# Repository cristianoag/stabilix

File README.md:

# Stabilix

Stabilix is a spin-off of the self-balancing robot project called B-ROBOT EVO created by JJ Robotics. 

It is a platform for experiments with different sensors and algorithms. The robot is able to balance itself on two wheels and move around avoiding obstacles. The robot is based on ESP32 and it is remotely controlled using a smartphone via Bluetooth.

## Hardware

The robot is based on ESP32 microcontroller and it is remotely controlled using a smartphone via Bluetooth. The robot is equipped with the following hardware components:

* 1 x MPU6050 - 6-axis accelerometer and gyroscope
* 2 x NEMA17 stepper motors
* 2 x A4988 stepper motor drivers
* 1 x ESP32 microcontroller

The robot is powered by a 7.4V LIPO battery pack. The battery is connected to a voltage regulator that converts the voltage to 5V. The 5V is used to power the ESP32 microcontroller and the stepper motor drivers. The stepper motors are powered directly from the battery.

## Assembly

The robot is assembled using 3D printed parts. The 3D models are available in the `3D_models` folder. The robot is assembled using the following parts:

### Bill of materials

| Part name | Quantity | Link |
| --- | --- | --- |
| 3D printed parts | 1 | [Thingiverse](https://www.thingiverse.com/thing:2786294) |

## Software

The robot is programmed in C++ using Arduino IDE. The code is based on the B-ROBOT EVO project created by JJ Robotics. 

## Installation

1. Download and install Arduino IDE from [here](https://www.arduino.cc/en/software)
2. Download and install ESP32 board support for Arduino IDE from [here]()
3. Download the code from this repository and open it in Arduino IDE
4. Connect the robot to your computer using a USB cable
5. Select the correct board and port in Arduino IDE
6. Upload the code to the robot

## Usage

1. Download and install the B-ROBOT EVO app from [here](https://play.google.com/store/apps/details?id=com.jjrobots.brobotevoremotecontrol&hl=en&gl=US)

2. Turn on the robot and connect to it using the app

3. Use the app to control the robot

## Contributing

Pull requests are welcome. For major changes, please open an issue first to discuss what you would like to change.

## License

This work is licensed under the CERN OHL-S v2. You may redistribute and modify this project and its documentation under the terms of the CERN-OHL-S v2.

This project is distributed WITHOUT ANY EXPRESS OR IMPLIED WARRANTY, INCLUDING OF MERCHANTABILITY, SATISFACTORY QUALITY AND FITNESS FOR A PARTICULAR PURPOSE. Please see the CERN-OHL-S v2 for applicable conditions.

You should have received a copy of the CERN-OHL-S along with this project. If not, see <https://ohwr.org/project/cernohl/wikis/Documents/CERN-OHL-version-2>.

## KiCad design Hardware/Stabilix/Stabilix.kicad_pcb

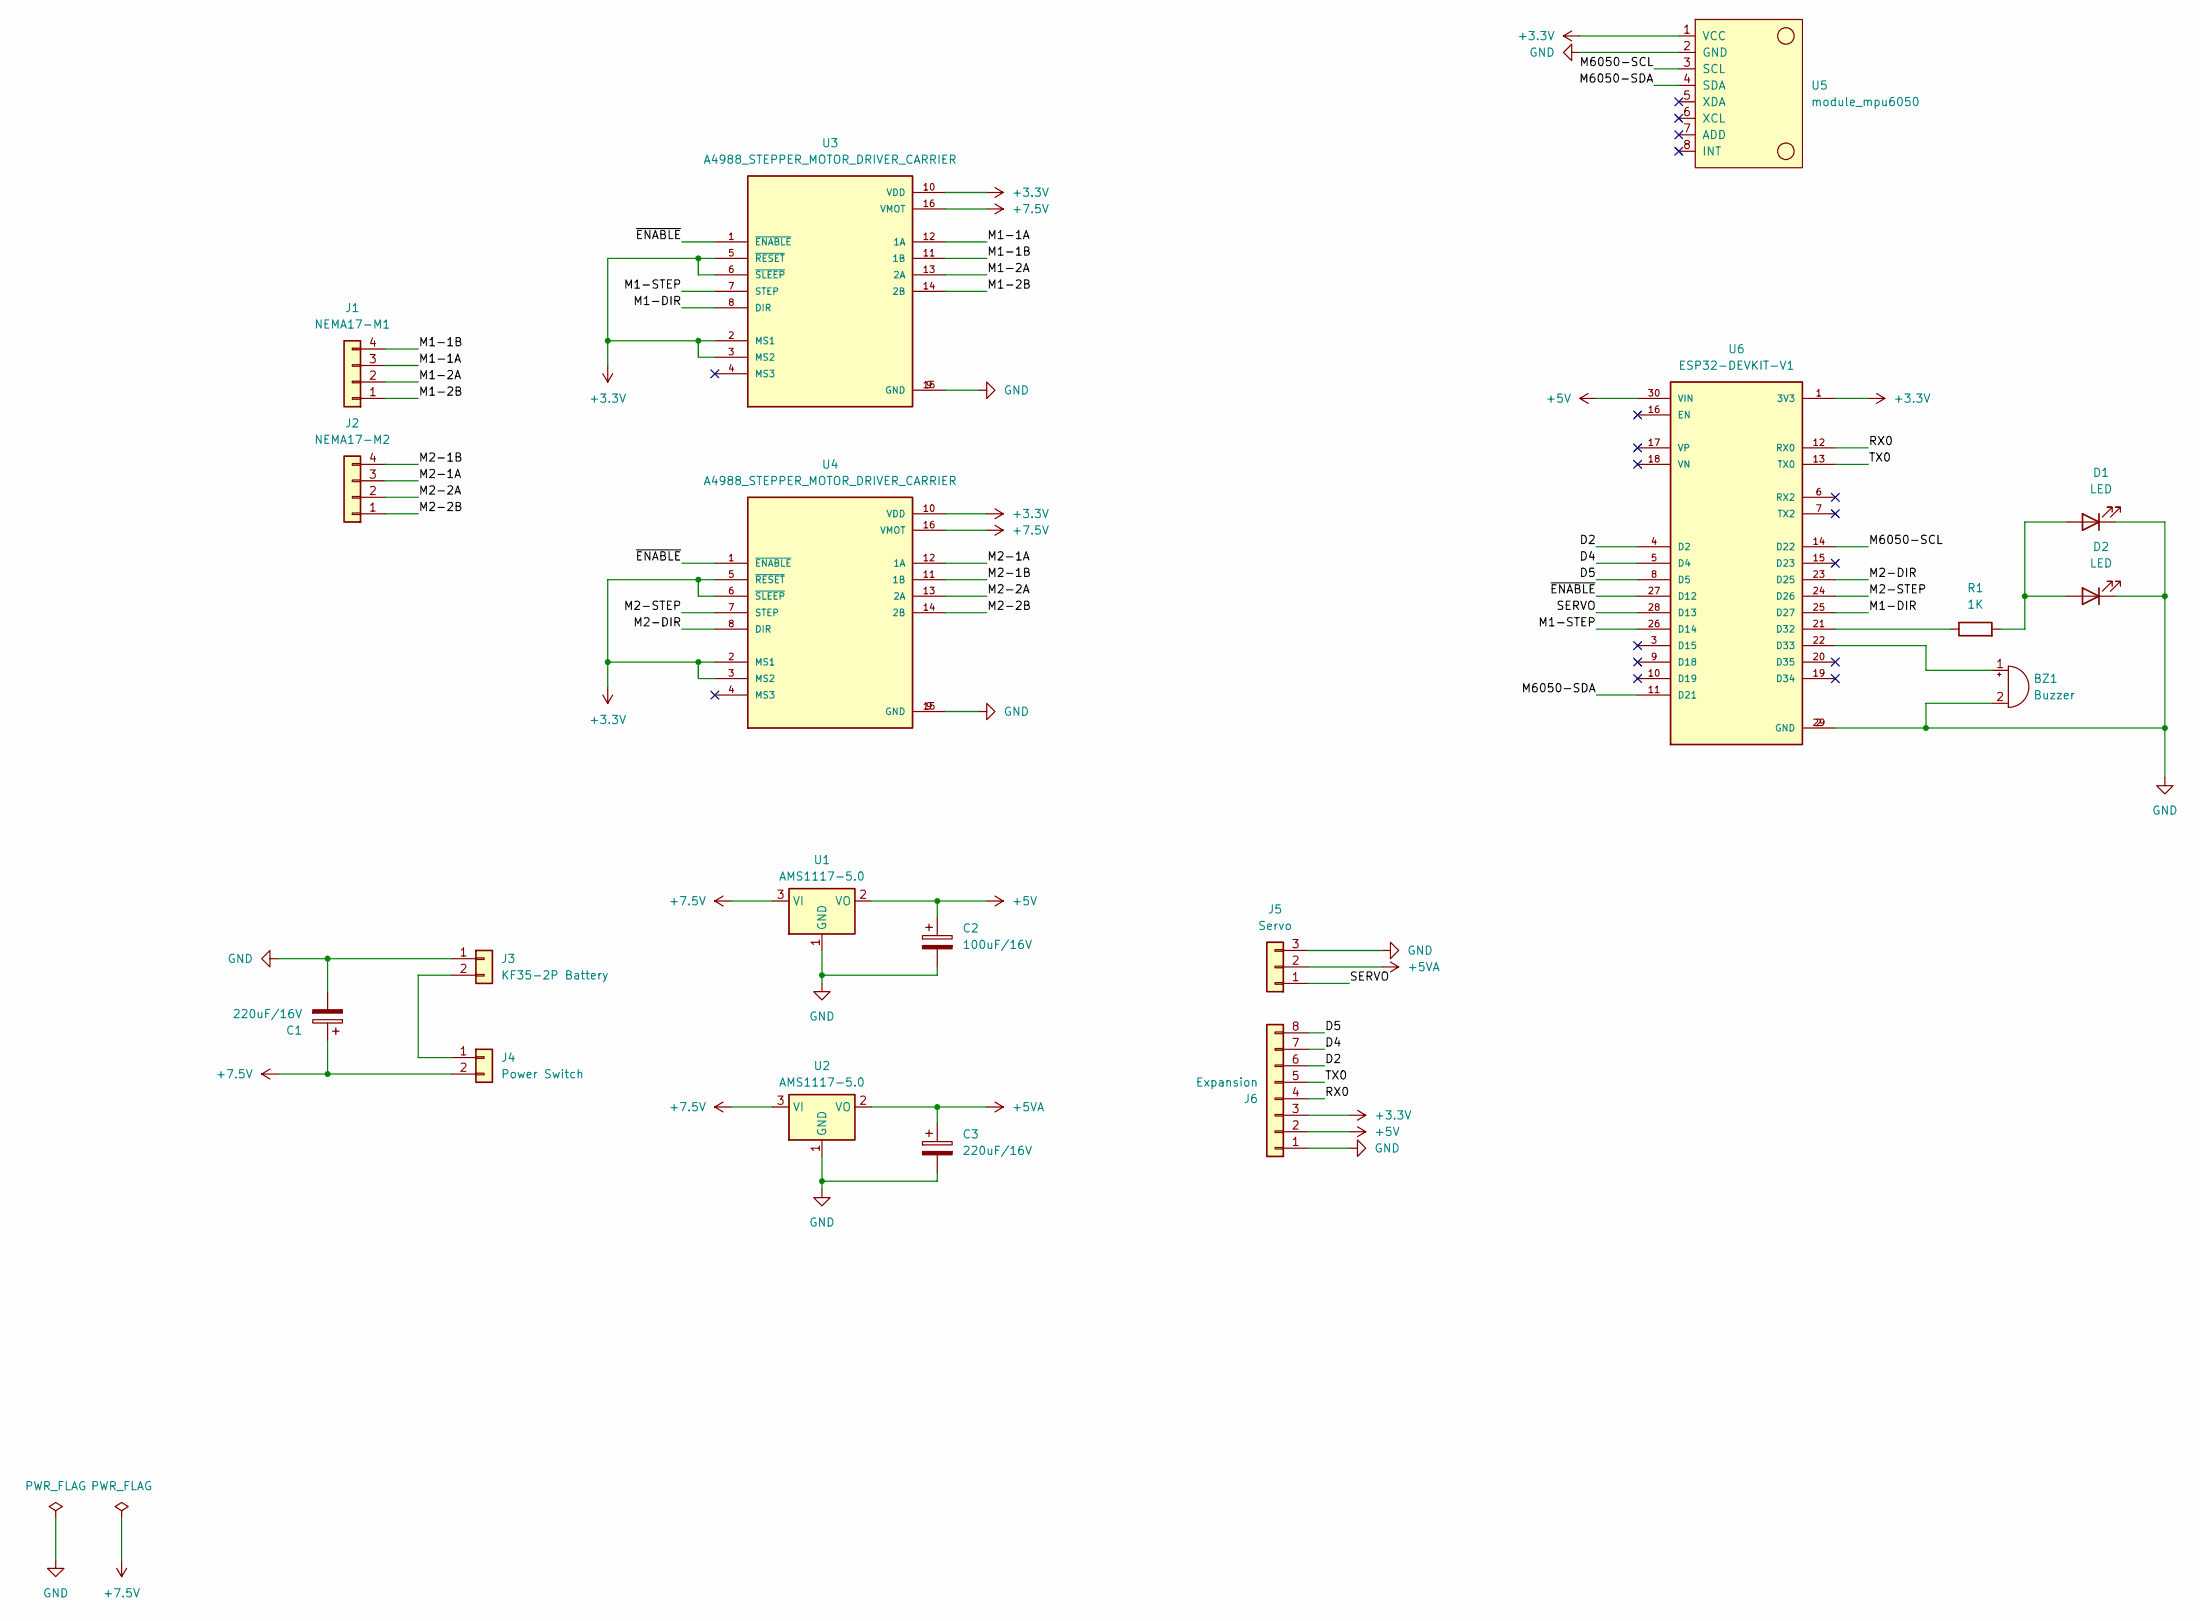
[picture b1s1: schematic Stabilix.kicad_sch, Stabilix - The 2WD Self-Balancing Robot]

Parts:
BZ1: Buzzer; Buzzer_12x9.5RM7.6
C1, C3: 220uF/16V; CP_Radial_D6.3mm_P2.50mm
C2: 100uF/16V; CP_Radial_D5.0mm_P2.50mm
D1, D2: LED; LED_D3.0mm
J1: NEMA17-M1; PinHeader_1x04_P2.54mm_Vertical
J2: NEMA17-M2; PinHeader_1x04_P2.54mm_Vertical
J3: KF35-2P Battery; TerminalBlock_bornier-2_P5.08mm
J4: Power Switch; PinHeader_1x02_P2.54mm_Vertical
J5: Servo; PinHeader_1x03_P2.54mm_Vertical
J6: Expansion; PinHeader_2x04_P2.54mm_Vertical
R1: 1K; R_Axial_DIN0207_L6.3mm_D2.5mm_P10.16mm_Horizontal
U1, U2: AMS1117-5.0; SOT-223-3_TabPin2
U3, U4: A4988_STEPPER_MOTOR_DRIVER_CARRIER; MODULE_A4988_STEPPER_MOTOR_DRIVER_CARRIER
U5: module_mpu6050
U6: ESP32-DEVKIT-V1; MODULE_ESP32_DEVKIT_V1; PARTREV N/A

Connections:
+3.3V: J6.3, U3.2 (MS1), U3.3 (MS2), U3.5 (~RESET), U3.6 (~SLEEP), U3.10 (VDD), U4.2 (MS1), U4.3 (MS2), U4.5 (~RESET), U4.6 (~SLEEP), U4.10 (VDD), U5.1 (VCC), U6.1 (3V3)
+5V: C2.1, J6.2, U1.2 (VO), U6.30 (VIN)
+5VA: C3.1, J5.2, U2.2 (VO)
+7.5V: C1.1, J4.2, U1.3 (VI), U2.3 (VI), U3.16 (VMOT), U4.16 (VMOT)
/D2: J6.6, U6.4 (D2)
/D4: J6.7, U6.5 (D4)
/D5: J6.8, U6.8 (D5)
/M1-1A: J1.3, U3.12 (1A)
/M1-1B: J1.4, U3.11 (1B)
/M1-2A: J1.2, U3.13 (2A)
/M1-2B: J1.1, U3.14 (2B)
/M1-DIR: U3.8 (DIR), U6.25 (D27)
/M1-STEP: U3.7 (STEP), U6.26 (D14)
/M2-1A: J2.3, U4.12 (1A)
/M2-1B: J2.4, U4.11 (1B)
/M2-2A: J2.2, U4.13 (2A)
/M2-2B: J2.1, U4.14 (2B)
/M2-DIR: U4.8 (DIR), U6.23 (D25)
/M2-STEP: U4.7 (STEP), U6.24 (D26)
/M6050-SCL: U5.3 (SCL), U6.14 (D22)
/M6050-SDA: U5.4 (SDA), U6.11 (D21)
/RX0: J6.4, U6.12 (RX0)
/SERVO: J5.1, U6.28 (D13)
/TX0: J6.5, U6.13 (TX0)
/~ENABLE: U3.1 (~ENABLE), U4.1 (~ENABLE), U6.27 (D12)
GND: BZ1.2 (+), C1.2, C2.2, C3.2, D1.1 (K), D2.1 (K), J3.1, J5.3, J6.1, U1.1 (GND), U2.1 (GND), U3.9 (GND), U3.15 (GND), U4.9 (GND), U4.15 (GND), U5.2 (GND), U6.2 (GND), U6.29 (GND)
unnamed: BZ1.1 (-), U6.22 (D33)
unnamed: D1.2 (A), D2.2 (A), R1.2
unnamed: J3.2, J4.1
unnamed: R1.1, U6.21 (D32)

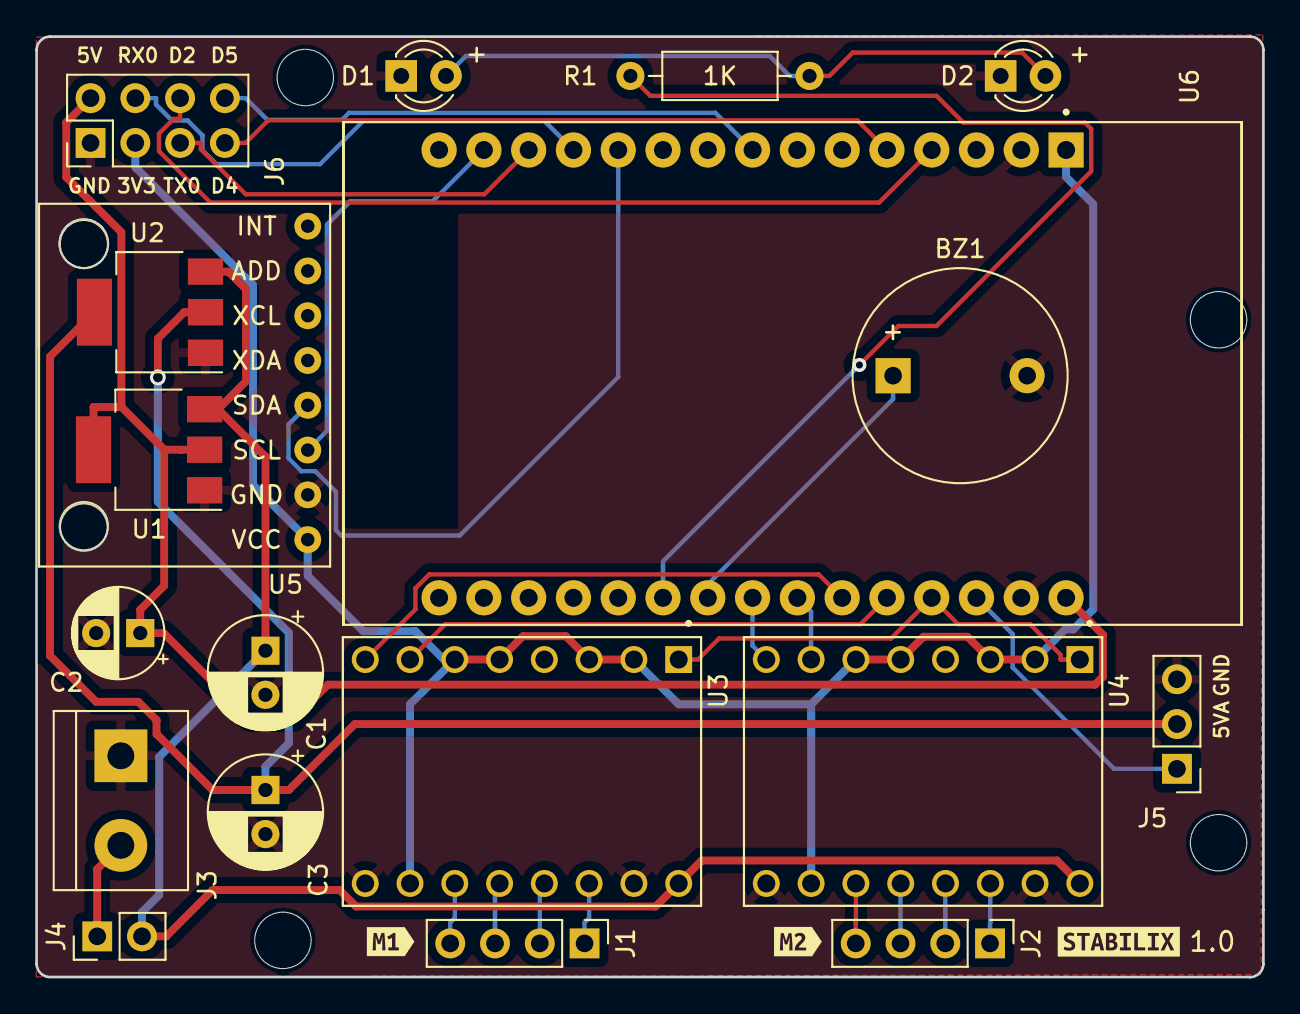
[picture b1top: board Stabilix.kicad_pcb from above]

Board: 2 copper layers, 69.6 x 53.3 mm, 26 parts (0 on the bottom side), 30 nets.

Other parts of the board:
MH1, MH2, MH4, MH4#2: MountingHole_3.2mm
kibuzzard-6589FCE6: G***; kibuzzard-6589FCE6
kibuzzard-6589FE3E: G***; kibuzzard-6589FE3E
kibuzzard-6589FE5A: G***; kibuzzard-6589FE5A

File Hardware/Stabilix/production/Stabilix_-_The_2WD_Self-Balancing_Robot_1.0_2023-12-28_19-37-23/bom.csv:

Designator,Footprint,Quantity,Value,LCSC Part #
BZ1,Buzzer_12x9.5RM7.6,1,Buzzer,
"C1, C3",CP_Radial_D6.3mm_P2.50mm,2,220uF/16V,
C2,CP_Radial_D5.0mm_P2.50mm,1,100uF/16V,
"D1, D2",LED_D3.0mm,2,LED,
J1,PinHeader_1x04_P2.54mm_Vertical,1,NEMA17-M1,
J2,PinHeader_1x04_P2.54mm_Vertical,1,NEMA17-M2,
J3,TerminalBlock_bornier-2_P5.08mm,1,KF35-2P Battery,
J4,PinHeader_1x02_P2.54mm_Vertical,1,Power Switch,
J5,PinHeader_1x03_P2.54mm_Vertical,1,Servo,
J6,PinHeader_2x04_P2.54mm_Vertical,1,Expansion,
R1,R_Axial_DIN0207_L6.3mm_D2.5mm_P10.16mm_Horizontal,1,1K,
"U1, U2",SOT-223-3_TabPin2,2,AMS1117-5.0,
"U3, U4",MODULE_A4988_STEPPER_MOTOR_DRIVER_CARRIER,2,A4988_STEPPER_MOTOR_DRIVER_CARRIER,
U5,module_mpu6050,1,module_mpu6050,
U6,MODULE_ESP32_DEVKIT_V1,1,ESP32-DEVKIT-V1,

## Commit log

2023-12-25 Initial load
2023-12-25 Footprint adjustments
2023-12-29 fixes on the screw holes
2023-12-29 License
